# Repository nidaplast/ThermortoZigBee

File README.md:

# ThermortoZigBee - Conversion des radiateurs Thermor IO-homecontrol vers Zigbee

## 🎯 Objectif

Ce projet permet de remplacer complètement l'électronique de contrôle des radiateurs Thermor Emotion 4 (IO-homecontrol) par un ESP32-C6 avec support Zigbee natif, offrant :

- ✅ Intégration native Zigbee 3.0 (Home Assistant, Zigbee2MQTT)
- ✅ Contrôle précis de la puissance (0-100% par modulation de phase)
- ✅ Algorithmes avancés (PID, détection fenêtre, apprentissage)
- ✅ Capteurs intégrés (température, présence, consommation)
- ✅ Interface utilisateur conservée (écran, boutons)
- ✅ Sécurité renforcée (isolation galvanique, watchdog)

## 📋 Prérequis

### Matériel
- ESP32-C6-DevKitC-1 ou module ESP32-C6-WROOM-1
- MOC3063 (optotriac) + BTA16-600B (triac)
- Alimentation AC/DC 3.3V isolée (HLK-PM03)
- Capteur température DS18B20 ou NTC
- Composants passifs (voir BOM)

### Logiciel
- ESP-IDF v5.2+ avec support Zigbee
- KiCad 7.0+ pour les PCB
- Home Assistant avec ZHA ou Zigbee2MQTT

## 🚀 Installation rapide

```bash
# Clone du projet
git clone https://github.com/yourusername/ThermortoZigBee.git
cd ThermortoZigBee

# Configuration ESP-IDF
idf.py set-target esp32c6
idf.py menuconfig

# Compilation et flash
idf.py build
idf.py -p /dev/ttyUSB0 flash monitor
```

## 📁 Structure du projet

```
ThermortoZigBee/
├── firmware/           # Code ESP32-C6
│   ├── main/          # Application principale
│   └── components/    # Modules (zigbee, sensors, etc.)
├── hardware/          # Conception PCB
│   ├── kicad/        # Fichiers KiCad
│   └── gerbers/      # Fichiers de production
├── docs/             # Documentation détaillée
├── home-assistant/   # Configurations YAML
└── tools/           # Scripts utilitaires
```

## ⚡ Fonctionnalités principales

### Contrôle de puissance
- Modulation de phase 0-100% (résolution 1%)
- Protection contre les surintensités
- Détection passage par zéro

### Capteurs
- Température ambiante (±0.5°C)
- Détection de présence PIR
- Mesure consommation instantanée
- Détection fenêtre ouverte

### Modes de fonctionnement
- **Confort** : Température de consigne normale
- **Éco** : Réduction de -3.5°C
- **Hors-gel** : Maintien à 7°C
- **Boost** : Chauffe rapide temporaire
- **Programmation** : Planning hebdomadaire

### Intégration Zigbee
- Device Type : Thermostat (0x0301)
- Clusters supportés :
  - Basic (0x0000)
  - Power Configuration (0x0001)
  - Thermostat (0x0201)
  - Occupancy Sensing (0x0406)
  - Electrical Measurement (0x0B04)

## 🔧 Configuration

### 1. Appairage Zigbee
```yaml
# Maintenez le bouton BOOT pendant 5 secondes
# La LED clignote rapidement = mode appairage
```

### 2. Home Assistant
```yaml
climate:
  - platform: mqtt
    name: "Radiateur Salon"
    modes: ["heat", "off"]
    preset_modes: ["comfort", "eco", "away", "boost"]
```

### 3. Paramètres avancés
Via l'interface web locale ou Zigbee :
- Coefficients PID
- Seuils de détection
- Courbe de chauffe

## 📊 Performances

| Paramètre | Valeur |
|-----------|---------|
| Consommation veille | < 0.5W |
| Temps de réponse | < 100ms |
| Précision température | ±0.5°C |
| Résolution puissance | 1% |
| Portée Zigbee | 10-30m |

## 🛡️ Sécurité

- ⚠️ **DANGER** : Intervention sur du 230V
- Isolation galvanique obligatoire
- Protection thermique intégrée
- Watchdog hardware
- Mode failsafe automatique

## 🤝 Contribution

Les contributions sont les bienvenues ! Voir [CONTRIBUTING.md](docs/CONTRIBUTING.md)

## 📝 Licence

Ce projet est sous licence CeCILL - voir [LICENSE](LICENSE)

## 🙏 Remerciements

- Communauté ESP32 et Espressif
- Projet Zigbee2MQTT
- Forum Home Assistant France

---

**⚠️ AVERTISSEMENT** : Ce projet implique des modifications sur des appareils 230V. L'installation doit être réalisée par une personne qualifiée. L'auteur décline toute responsabilité en cas de dommage.

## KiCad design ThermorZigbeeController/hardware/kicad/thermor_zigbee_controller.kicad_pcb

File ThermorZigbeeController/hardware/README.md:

# Hardware Design - Thermor Zigbee Controller

## Vue d'ensemble

Ce dossier contient tous les fichiers nécessaires pour la fabrication du PCB de remplacement pour les radiateurs Thermor Emotion 4.

## Structure des fichiers

```
hardware/
├── kicad/
│   ├── thermor_zigbee_controller.kicad_pro    # Projet KiCad
│   ├── thermor_zigbee_controller.kicad_sch    # Schéma électronique
│   ├── thermor_zigbee_controller.kicad_pcb    # Circuit imprimé
│   ├── thermor_zigbee_controller.kicad_prl    # Préférences locales
│   ├── thermor_zigbee_controller.net          # Netlist
│   ├── thermor_zigbee_controller-cache.lib    # Cache des symboles
│   ├── fp-lib-table                           # Table des empreintes
│   ├── sym-lib-table                          # Table des symboles
│   └── Thermor_Custom.lib                     # Bibliothèque custom
├── fabrication/
│   ├── gerbers/                               # Fichiers Gerber pour fab
│   ├── drill/                                 # Fichiers de perçage
│   └── assembly/                              # Fichiers d'assemblage
├── 3d/
│   └── thermor_controller_3d.png              # Vue 3D du PCB
├── BOM.csv                                    # Liste des composants
└── README.md                                  # Ce fichier
```

## Spécifications du PCB

- **Dimensions** : 80 x 60 mm
- **Nombre de couches** : 2
- **Épaisseur** : 1.6 mm
- **Finition** : HASL sans plomb
- **Couleur** : Vert (masque), Blanc (sérigraphie)
- **Via minimum** : 0.3 mm
- **Piste minimum** : 0.2 mm

## Composants principaux

| Référence | Composant | Description |
|-----------|-----------|-------------|
| U1 | ESP32-C6-WROOM-1 | Microcontrôleur principal avec Zigbee |
| U2 | HT1621 | Contrôleur LCD 7 segments |
| U3-U5 | PC817 | Optocoupleurs isolation triacs |
| U6 | AMS1117-3.3 | Régulateur 3.3V |
| J1 | JST-XH 3P | Connecteur capteur PIR |
| J2 | JST-XH 6P | Connecteur carte puissance |
| J3 | FPC 20P | Connecteur LCD |
| J4 | JST-XH 8P | Connecteur boutons |

## Instructions de fabrication

### 1. Génération des Gerbers (KiCad 7.0+)

1. Ouvrir `thermor_zigbee_controller.kicad_pcb`
2. Fichier → Tracer → Format Gerber
3. Cocher les couches :
   - F.Cu (Cuivre face avant)
   - B.Cu (Cuivre face arrière)
   - F.Paste (Pâte à braser avant)
   - B.Paste (Pâte à braser arrière)
   - F.SilkS (Sérigraphie avant)
   - B.SilkS (Sérigraphie arrière)
   - F.Mask (Masque soudure avant)
   - B.Mask (Masque soudure arrière)
   - Edge.Cuts (Contour PCB)
4. Générer aussi les fichiers de perçage

### 2. Commande chez JLCPCB/PCBWay

1. Zipper tous les Gerbers
2. Uploader sur le site du fabricant
3. Spécifications recommandées :
   - 2 couches
   - 1.6mm épaisseur
   - HASL sans plomb
   - Vert/Blanc
   - Quantité : 5-10 pièces

### 3. Assemblage

#### Ordre de soudure recommandé :
1. **Composants CMS côté TOP** :
   - ESP32-C6 (utiliser flux et air chaud)
   - Résistances/condensateurs 0805
   - Régulateur AMS1117
   - HT1621 si CMS

2. **Composants traversants** :
   - Optocoupleurs PC817
   - Connecteurs JST
   - Condensateurs électrolytiques

3. **Test avant connexion** :
   - Vérifier courts-circuits
   - Tester alimentation 3.3V
   - Programmer ESP32 avec firmware de test

## Points d'attention

### Isolation galvanique
- Les optocoupleurs PC817 assurent l'isolation entre 230V et basse tension
- Respecter un espacement minimum de 3mm entre les zones
- Ne pas router de pistes sous les optocoupleurs

### Thermique
- L'ESP32-C6 peut chauffer légèrement
- Prévoir des vias thermiques sous le module
- Espacer du régulateur de tension

### CEM (Compatibilité Électromagnétique)
- Plan de masse continu côté BOTTOM
- Condensateurs de découplage proches des IC
- Pistes courtes pour signaux rapides

## Modifications possibles

1. **Version mini** (60x40mm) :
   - Retirer certains connecteurs
   - Utiliser ESP32-C6 bare chip

2. **Version pro** avec :
   - Mesure de puissance intégrée
   - RTC avec supercap
   - Antenne externe

## Tests de validation

Liste de vérification avant utilisation :

- [ ] Continuité masse
- [ ] Isolation 230V/3.3V > 1MΩ
- [ ] Tension 3.3V stable
- [ ] Communication LCD fonctionnelle
- [ ] Lecture boutons OK
- [ ] Détection PIR active
- [ ] Commande triacs (avec simulateur)
- [ ] Communication Zigbee

## Support

Pour toute question sur le hardware :
- Vérifier les datasheets des composants
- Consulter le schéma annoté
- Tester avec le firmware de test basique

## Licence

Ce design hardware est publié sous licence Open Hardware.
Vous êtes libre de le modifier et l'utiliser.

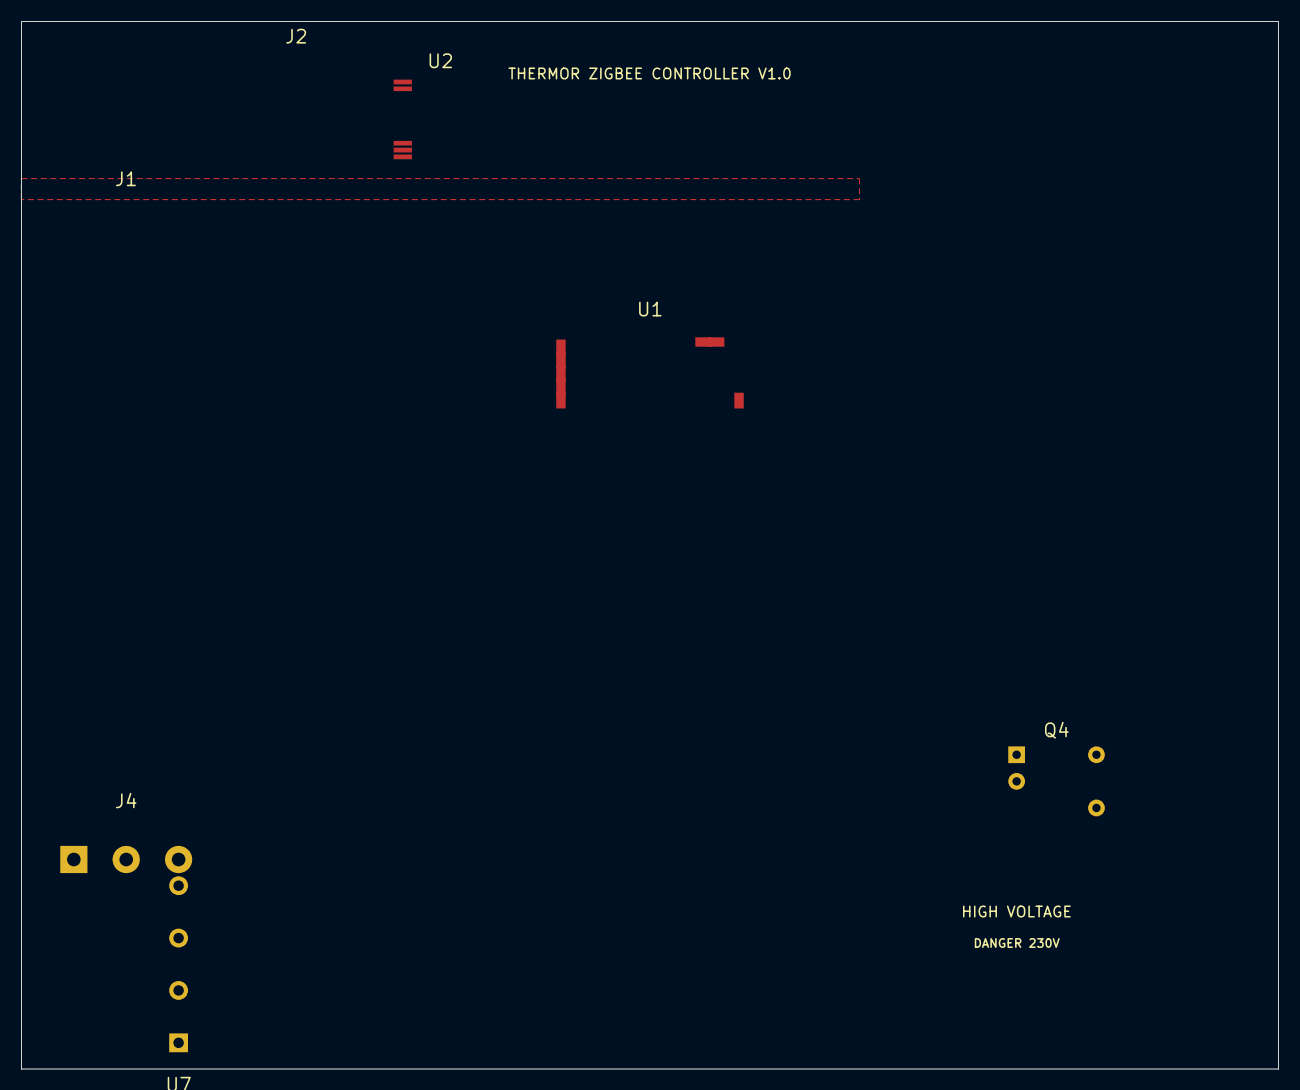
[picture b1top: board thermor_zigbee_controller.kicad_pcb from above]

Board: 2 copper layers, 120.0 x 100.0 mm, 7 parts (0 on the bottom side), 7 nets, no tracks yet.

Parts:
J1: USB-C; USB_C_Receptacle_USB2.0
J2: LCD_Conn; JST_XH_B6B-XH-A_1x06_P2.50mm_Vertical
J4: AC_Input; TerminalBlock_Phoenix_MKDS-1,5-3_1x03_P5.00mm_Horizontal
Q4: MOC3021; DIP-6_W7.62mm
U1: ESP32-C6-WROOM-1
U2: HT1621; SSOP-28_5.3x10.2mm_P0.65mm
U7: HLK-PM03; Converter_ACDC_HiLink_HLK-PMxx

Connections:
+3V3: U1.1, U2.1, U7.4
AC_L: J4.1, U7.1
AC_N: J4.2, U7.2
GND: U1.20, U2.2, U7.3
LCD_CS: U1.3, U2.10
LCD_DATA: U1.5, U2.12
LCD_WR: U1.4, U2.11

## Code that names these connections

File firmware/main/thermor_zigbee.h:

/**
 * @file thermor_zigbee.h
 * @brief Main header file for Thermor Zigbee Controller
 * @date 2024-01-15
 * 
 * ESP32-C6 based Zigbee controller for Thermor Emotion 4 heaters
 * Provides native Zigbee support with advanced heating control
 */

#ifndef THERMOR_ZIGBEE_H
#define THERMOR_ZIGBEE_H

#include <stdio.h>
#include <stdint.h>
#include <stdbool.h>
#include "freertos/FreeRTOS.h"
#include "freertos/task.h"
#include "freertos/queue.h"
#include "freertos/semphr.h"
#include "esp_log.h"
#include "esp_err.h"
#include "esp_system.h"

// GPIO Pin Definitions (matching KiCad schematic)
#define GPIO_TRIAC_CONTROL      GPIO_NUM_4   // IO4 - Triac control via optocoupler
#define GPIO_ZERO_CROSS        GPIO_NUM_5    // IO5 - Zero crossing detection
#define GPIO_TEMP_SENSOR       GPIO_NUM_6    // IO6 - Temperature sensor (1-Wire or I2C)
#define GPIO_PIR_SENSOR        GPIO_NUM_7    // IO7 - PIR motion sensor input
#define GPIO_LCD_CS            GPIO_NUM_8    // IO8 - HT1621 LCD Chip Select
#define GPIO_LCD_WR            GPIO_NUM_9    // IO9 - HT1621 LCD Write
#define GPIO_LCD_DATA          GPIO_NUM_10   // IO10 - HT1621 LCD Data
#define GPIO_BTN_ROW1          GPIO_NUM_11   // IO11 - Button matrix row 1
#define GPIO_BTN_ROW2          GPIO_NUM_12   // IO12 - Button matrix row 2
#define GPIO_BTN_ROW3          GPIO_NUM_13   // IO13 - Button matrix row 3
#define GPIO_BTN_COL1          GPIO_NUM_18   // IO18 - Button matrix column 1
#define GPIO_BTN_COL2          GPIO_NUM_19   // IO19 - Button matrix column 2
#define GPIO_BTN_COL3          GPIO_NUM_20   // IO20 - Button matrix column 3
#define GPIO_STATUS_LED        GPIO_NUM_21   // IO21 - Status LED
#define GPIO_WINDOW_SENSOR     GPIO_NUM_22   // IO22 - Window open detection
#define GPIO_PRESENCE_OVERRIDE GPIO_NUM_23   // IO23 - Manual presence override

// System Configuration
#define MAIN_TASK_STACK_SIZE    4096
#define MAIN_TASK_PRIORITY      5
#define TEMP_TASK_STACK_SIZE    2048
#define TEMP_TASK_PRIORITY      4
#define UI_TASK_STACK_SIZE      3072
#define UI_TASK_PRIORITY        3
#define ZIGBEE_TASK_STACK_SIZE  4096
#define ZIGBEE_TASK_PRIORITY    6

// Temperature Control Parameters
#define TEMP_MIN_CELSIUS        5.0f
#define TEMP_MAX_CELSIUS        30.0f
#define TEMP_STEP_CELSIUS       0.5f
#define TEMP_HYSTERESIS         0.2f
#define TEMP_SAMPLE_PERIOD_MS   1000
#define TEMP_FILTER_SAMPLES     10

// Power Control Parameters
#define POWER_MIN_PERCENT       0
#define POWER_MAX_PERCENT       100
#define POWER_SOFT_START_MS     2000
#define ZERO_CROSS_TIMEOUT_MS   25    // 50Hz = 20ms period

// UI Configuration
#define BUTTON_DEBOUNCE_MS      50
#define BUTTON_LONG_PRESS_MS    1000
#define LCD_UPDATE_PERIOD_MS    200
#define BACKLIGHT_TIMEOUT_S     30

// Zigbee Configuration
#define ZIGBEE_CHANNEL_MASK     0x07FFF800  // Channels 11-26
#define MANUFACTURER_NAME       "DIY_Smart"
#define MODEL_IDENTIFIER        "THERMOR_ZB_1"
#define DEVICE_VERSION          1

// Operating Modes
typedef enum {
    MODE_OFF = 0,
    MODE_COMFORT,
    MODE_ECO,
    MODE_ANTI_FREEZE,
    MODE_PROGRAM,
    MODE_BOOST,
    MODE_VACATION
} heating_mode_t;

// System States
typedef enum {
    STATE_INIT = 0,
    STATE_IDLE,
    STATE_HEATING,
    STATE_ERROR,
    STATE_PAIRING,
    STATE_UPDATING
} system_state_t;

// Temperature Data Structure
typedef struct {
    float current;
    float target;
    float offset;
    bool valid;
    uint32_t last_update;
} temperature_data_t;

// Power Control Structure
typedef struct {
    uint8_t current_percent;
    uint8_t target_percent;
    bool soft_start_active;
    uint32_t soft_start_begin;
    uint32_t last_zero_cross;
    uint16_t phase_delay_us;
} power_control_t;

// Presence Detection Structure
typedef struct {
    bool pir_detected;
    bool manual_override;
    bool window_open;
    uint32_t last_motion;
    uint32_t absence_timer_min;
} presence_data_t;

// Program Schedule Entry
typedef struct {
    uint8_t hour;
    uint8_t minute;
    heating_mode_t mode;
    float temperature;
} schedule_entry_t;

// System Configuration Structure
typedef struct {
    heating_mode_t mode;
    system_state_t state;
    temperature_data_t temperature;
    power_control_t power;
    presence_data_t presence;
    schedule_entry_t schedule[7][6];  // 7 days, 6 entries per day
    bool child_lock;
    bool adaptive_start;
    bool open_window_detection;
    uint8_t lcd_brightness;
    uint16_t zigbee_short_addr;
} system_config_t;

// Global system configuration
extern system_config_t g_system_config;
extern SemaphoreHandle_t g_config_mutex;
extern QueueHandle_t g_event_queue;

// Event Types
typedef enum {
    EVENT_BUTTON_PRESS,
    EVENT_BUTTON_LONG_PRESS,
    EVENT_TEMP_UPDATE,
    EVENT_PRESENCE_CHANGE,
    EVENT_WINDOW_CHANGE,
    EVENT_ZIGBEE_CMD,
    EVENT_ZERO_CROSS,
    EVENT_TIMER_TICK
} event_type_t;

// Event Structure
typedef struct {
    event_type_t type;
    union {
        uint8_t button_id;
        float temperature;
        bool state;
        uint8_t zigbee_cmd;
    } data;
} system_event_t;

// Function Prototypes

// System Initialization
esp_err_t thermor_zigbee_init(void);
esp_err_t thermor_system_start(void);
void thermor_system_stop(void);

// Configuration Management
esp_err_t thermor_config_save(void);
esp_err_t thermor_config_load(void);
esp_err_t thermor_config_reset(void);

// Temperature Control
float thermor_get_current_temp(void);
float thermor_get_target_temp(void);
esp_err_t thermor_set_target_temp(float temp);
esp_err_t thermor_set_temp_offset(float offset);

// Mode Control
heating_mode_t thermor_get_mode(void);
esp_err_t thermor_set_mode(heating_mode_t mode);
const char* thermor_mode_to_string(heating_mode_t mode);

// Power Control
uint8_t thermor_get_power_percent(void);
esp_err_t thermor_set_power_percent(uint8_t percent);
esp_err_t thermor_enable_soft_start(bool enable);

// Presence Detection
bool thermor_is_presence_detected(void);
esp_err_t thermor_set_presence_override(bool override);
esp_err_t thermor_set_absence_timer(uint32_t minutes);

// Schedule Management
esp_err_t thermor_set_schedule(uint8_t day, uint8_t slot, schedule_entry_t *entry);
esp_err_t thermor_get_schedule(uint8_t day, uint8_t slot, schedule_entry_t *entry);
esp_err_t thermor_clear_schedule(void);

// System Control
esp_err_t thermor_set_child_lock(bool enable);
esp_err_t thermor_set_adaptive_start(bool enable);
esp_err_t thermor_set_window_detection(bool enable);
system_state_t thermor_get_system_state(void);

// Diagnostic Functions
esp_err_t thermor_run_self_test(void);
esp_err_t thermor_get_diagnostics(char *buffer, size_t len);
uint32_t thermor_get_uptime_seconds(void);
uint32_t thermor_get_energy_kwh(void);

// Utility Macros
#define THERMOR_CHECK(x) do {                              \
    esp_err_t __err = (x);                                 \
    if (__err != ESP_OK) {                                \
        ESP_LOGE(TAG, "Error %s at %s:%d",                \
                 esp_err_to_name(__err), __FILE__, __LINE__); \
        return __err;                                      \
    }                                                      \
} while(0)

#define THERMOR_CHECK_GOTO(x, label) do {                  \
    esp_err_t __err = (x);                                 \
    if (__err != ESP_OK) {                                \
        ESP_LOGE(TAG, "Error %s at %s:%d",                \
                 esp_err_to_name(__err), __FILE__, __LINE__); \
        goto label;                                        \
    }                                                      \
} while(0)

#endif // THERMOR_ZIGBEE_H

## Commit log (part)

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2025-06-02 Update LICENSE

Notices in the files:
README.md:
License: MIT
